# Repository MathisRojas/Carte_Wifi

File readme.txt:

Ce dossier contient l'ensemble des fichiers relatifs à la réalisation au projet :

1. Bilan produit

	Analyse de l'impact environnemental du projet (BBD 2011).

2. Diagrammes

	Inclut les différents schémas et diagrammes nécessaires à la compréhension du projet :

		Diagrammes des cas d'utilisation
		Diagrammes des exigences
		Algorigrammes

3. Documents utiles

	Regroupe les documents de référence et les documents techniques :

		Bibliographie

		Datasheets des composants utilisés :

			SHT21 (capteur d'humidité et de température)
			Relais
			ESP01 (module Wifi)

4. Electronique

	Documents et fichiers de conception électronique :

		Liste des composants électroniques utilisés (prix et référence fournisseur)
		Carte WiFi : fichier KiCad, typons, plan de perçage et d’implémentation, fichiers G-code et FlatCAM pour CNC
		Carte capteurs : fichier KiCad, typons, plan de perçage et d’implémentation

5. Planning

	Inclut le suivi du projet, le planning prévisionnel et l'état d'avancement des différentes étapes.

6. Programmes

	Contient les fichiers et codes liés aux développements logiciels :

		Carte WiFi : Programme C du microcontrôleur (PIC18F26K22)
		Application Node.js : scripts et fichiers de l'application

7.A la racine du dossier :

	Vidéo de présentation
	Manuel d'utilisation
	Rapport technique du projet

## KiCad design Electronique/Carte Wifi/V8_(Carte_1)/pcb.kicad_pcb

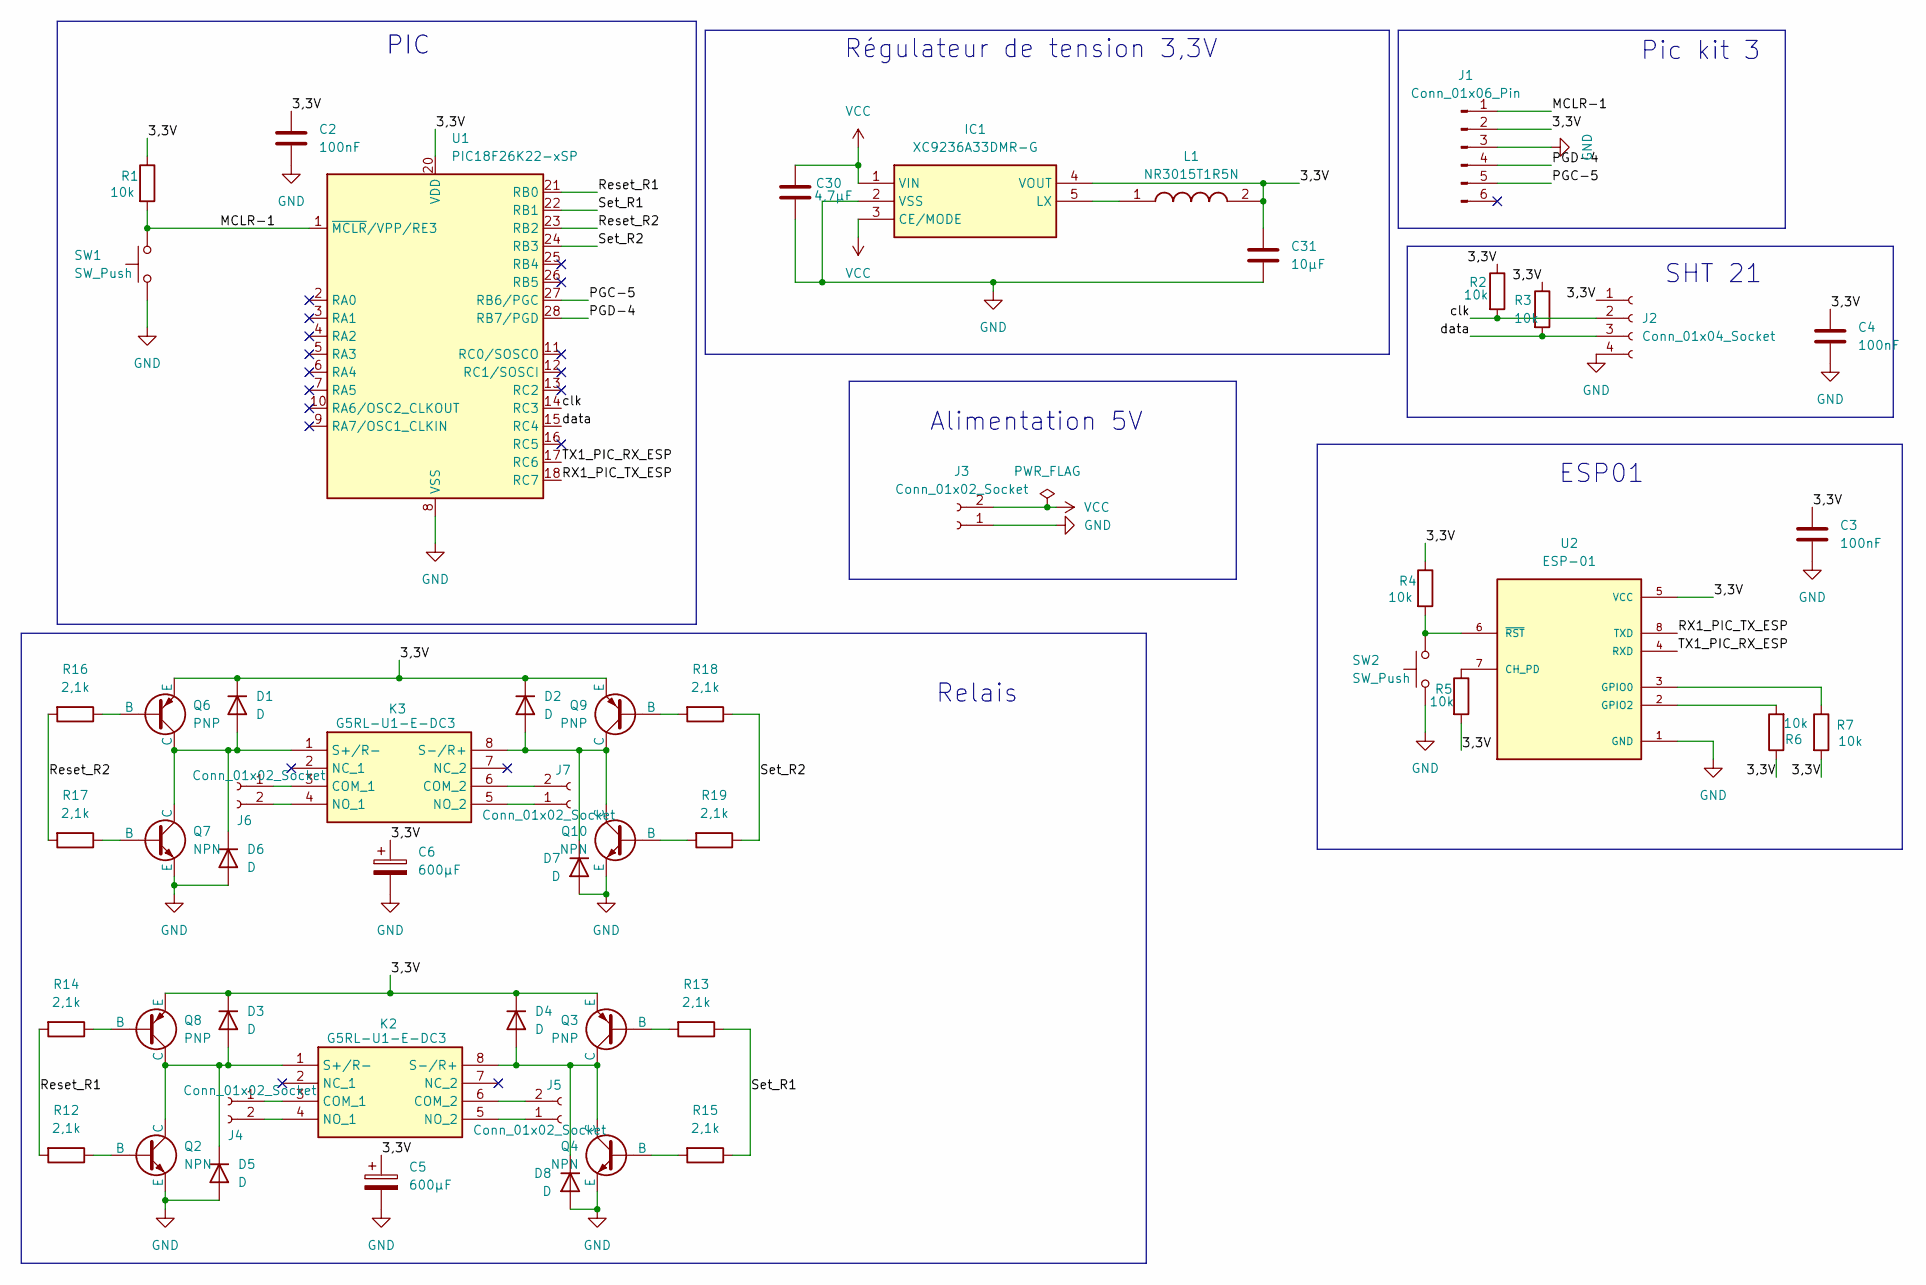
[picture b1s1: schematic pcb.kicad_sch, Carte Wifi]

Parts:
C2, C3, C4: 100nF; IUT_Capa_CMS_1206
C5, C6: 600µF; CP_Radial_D10.0mm_P5.00mm
C30: 4,7µF; IUT_Capa_CMS_1206
C31: 10µF; IUT_Capa_CMS_1206
D1, D2, D3, D4, D5, D6, D7, D8: D; IUT_Diode
IC1: XC9236A33DMR-G; SOT95P280X130-5N; Mouser Part Number 865-XC9236A33DMR-G
J1: Conn_01x06_Pin; IUT_SIL-6
J2: Conn_01x04_Socket; IUT_SIL-4
J3, J4, J5, J6, J7: Conn_01x02_Socket; IUT_bornier2
K2, K3: G5RL-U1-E-DC3; G5RLU1E; Mouser Part Number 653-G5RLU1EDC3
L1: NR3015T1R5N; NR3015; Mouser Part Number 963-NR3015T1R5N
Q2, Q4, Q7, Q10: NPN; 2SCR514RTL
Q3, Q6, Q8, Q9: PNP; SOT95P237X112-3N
R1, R2, R3, R4, R5, R6, R7: 10k; IUT_R4
R12, R13, R14, R15, R16, R17, R18, R19: 2,1k; IUT_R4
SW1, SW2: SW_Push; IUT_BP_petit
U1: PIC18F26K22-xSP; DIP-28_W7.62mm
U2: ESP-01; MODULE_ESP-01; PARTREV 1.0

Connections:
/3,3V: C2.1, C3.1, C4.1, C5.1, C6.1, C31.1, D1.1 (K), D2.1 (K), D3.1 (K), D4.1 (K), IC1.4 (VOUT), J1.2, J2.1, L1.2, Q3.2 (E), Q6.2 (E), Q8.2 (E), Q9.2 (E), R1.1, R2.1, R3.1, R4.1, R5.2, R6.1, R7.2, U1.20 (VDD), U2.5 (VCC)
/MCLR-1: J1.1, R1.2, SW1.2, U1.1 (~MCLR/VPP/RE3)
/PGC-5: J1.5, U1.27 (RB6/PGC)
/PGD-4: J1.4, U1.28 (RB7/PGD)
/RX1_PIC_TX_ESP: U1.18 (RC7), U2.8 (TXD)
/Reset_R1: R12.2, R14.2, U1.21 (RB0)
/Reset_R2: R16.2, R17.2, U1.23 (RB2)
/Set_R1: R13.1, R15.1, U1.22 (RB1)
/Set_R2: R18.1, R19.1, U1.24 (RB3)
/TX1_PIC_RX_ESP: U1.17 (RC6), U2.4 (RXD)
/clk: J2.2, R2.2, U1.14 (RC3)
/data: J2.3, R3.2, U1.15 (RC4)
GND: C2.2, C3.2, C4.2, C5.2, C6.2, C30.2, C31.2, D5.2 (A), D6.2 (A), D7.2 (A), D8.2 (A), IC1.2 (VSS), J1.3, J2.4, J3.1, Q2.2 (E), Q4.2 (E), Q7.2 (E), Q10.2 (E), SW1.1, SW2.1, U1.8 (VSS), U1.19 (VSS), U2.1 (GND)
unnamed: D1.2 (A), D6.1 (K), K3.1 (S+/R-), Q6.3 (C), Q7.3 (C)
unnamed: D2.2 (A), D7.1 (K), K3.8 (S-/R+), Q9.3 (C), Q10.3 (C)
unnamed: D3.2 (A), D5.1 (K), K2.1 (S+/R-), Q2.3 (C), Q8.3 (C)
unnamed: D4.2 (A), D8.1 (K), K2.8 (S-/R+), Q3.3 (C), Q4.3 (C)
unnamed: IC1.5 (LX), L1.1
unnamed: J4.1, K2.3 (COM_1)
unnamed: J4.2, K2.4 (NO_1)
unnamed: J5.1, K2.5 (NO_2)
unnamed: J5.2, K2.6 (COM_2)
unnamed: J6.1, K3.3 (COM_1)
unnamed: J6.2, K3.4 (NO_1)
unnamed: J7.1, K3.5 (NO_2)
unnamed: J7.2, K3.6 (COM_2)
unnamed: Q2.1 (B), R12.1
unnamed: Q3.1 (B), R13.2
unnamed: Q4.1 (B), R15.2
unnamed: Q6.1 (B), R16.1
unnamed: Q7.1 (B), R17.1
unnamed: Q8.1 (B), R14.1
unnamed: Q9.1 (B), R18.2
unnamed: Q10.1 (B), R19.2
unnamed: R5.1, U2.7 (CH_PD)
unnamed: R7.1, U2.3 (GPIO0)
unnamed: R6.2, U2.2 (GPIO2)
unnamed: R4.2, SW2.2, U2.6 (~RST)
VCC: C30.1, IC1.1 (VIN), IC1.3 (CE/MODE), J3.2

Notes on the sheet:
Relais
ESP01
Alimentation 5V
Régulateur de tension 3,3V
Pic kit 3
PIC
SHT 21

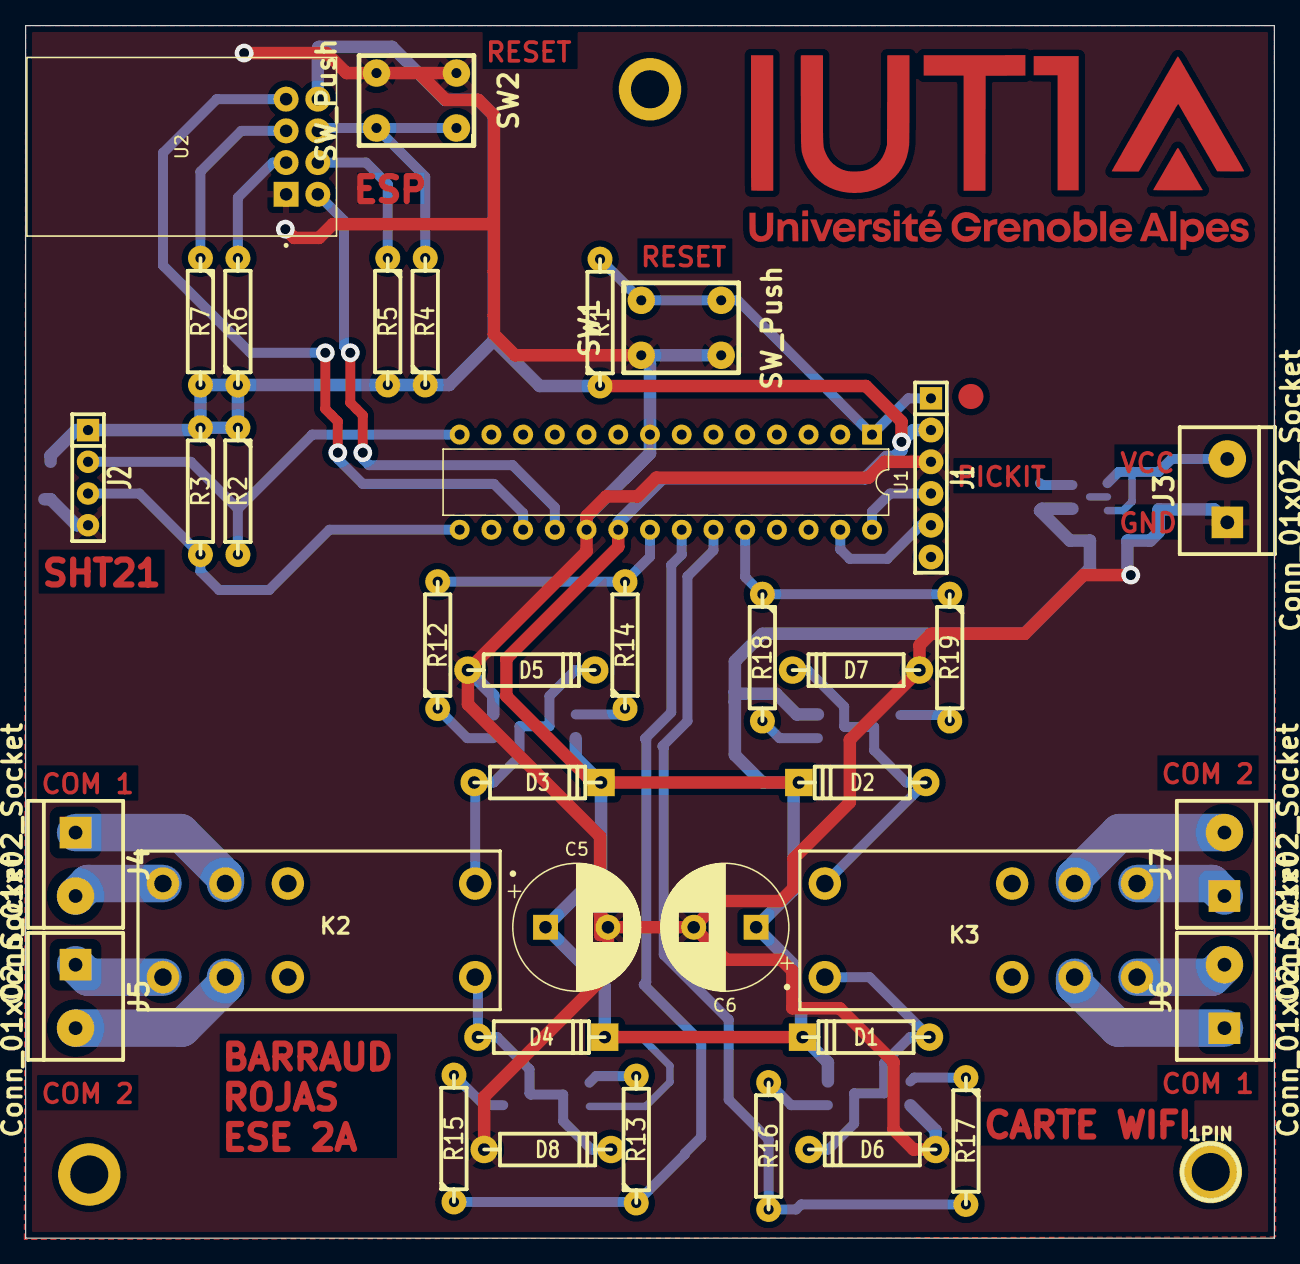
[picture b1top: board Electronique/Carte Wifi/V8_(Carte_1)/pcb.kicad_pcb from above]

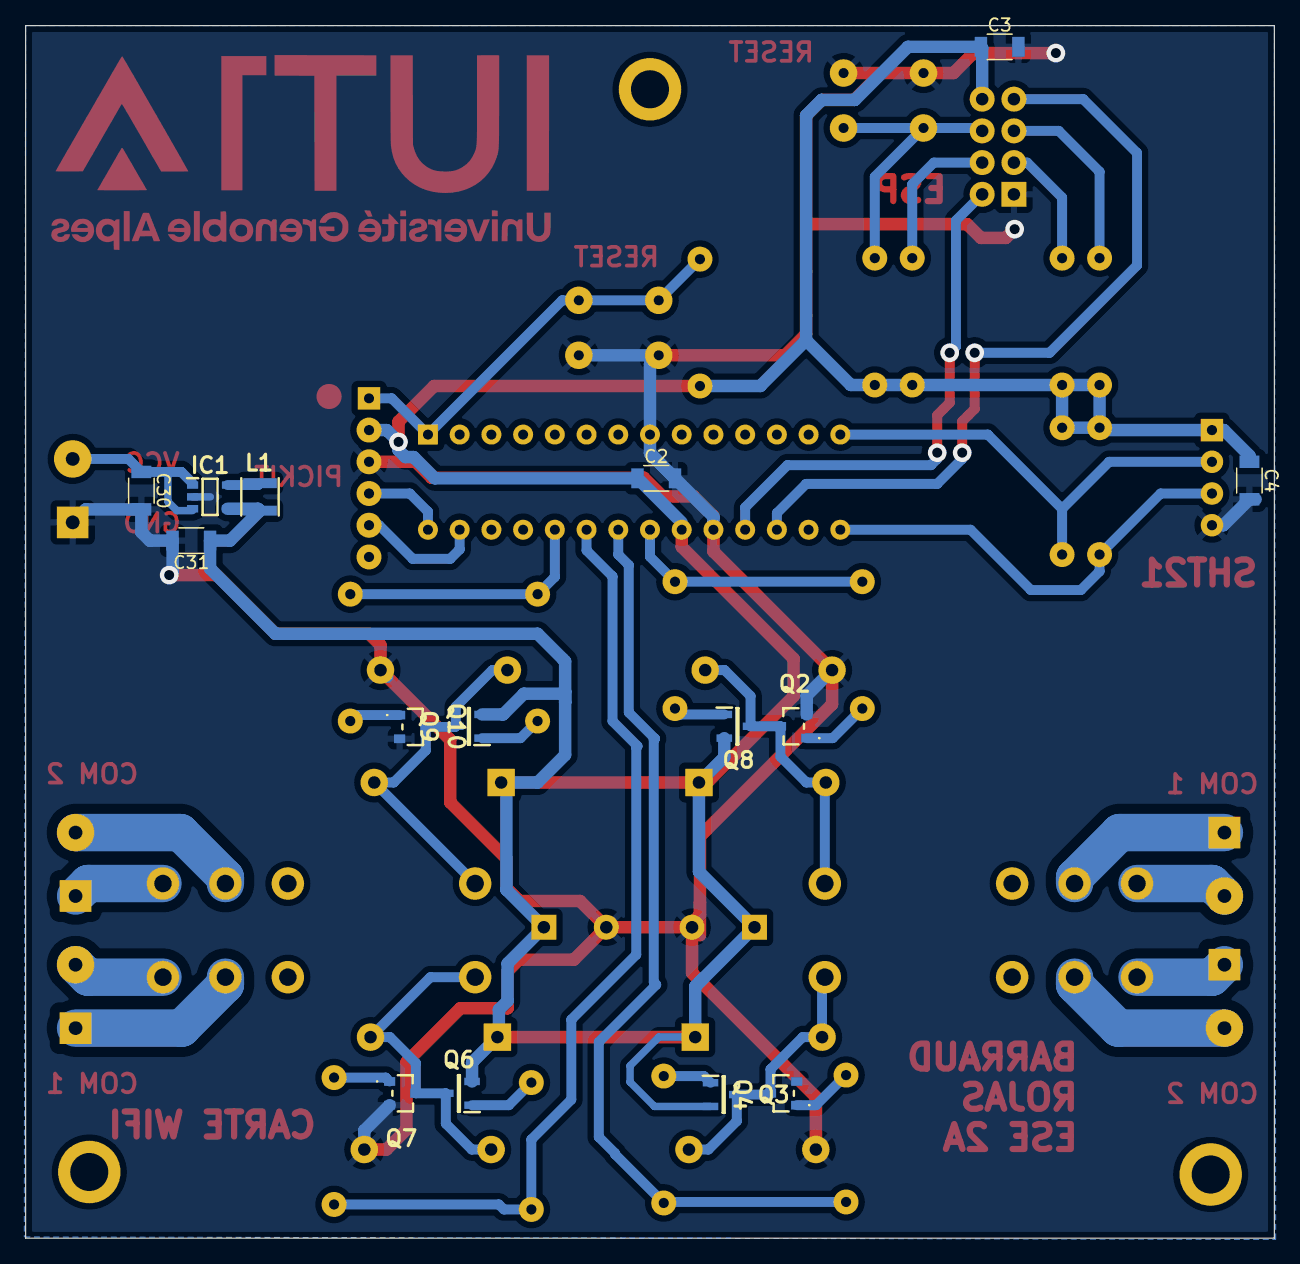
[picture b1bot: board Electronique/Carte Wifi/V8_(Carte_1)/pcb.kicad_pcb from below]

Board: 2 copper layers, 100.0 x 97.1 mm, 54 parts (15 on the bottom side), 39 nets.

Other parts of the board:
1PIN: P***; IUT_TrouFixation

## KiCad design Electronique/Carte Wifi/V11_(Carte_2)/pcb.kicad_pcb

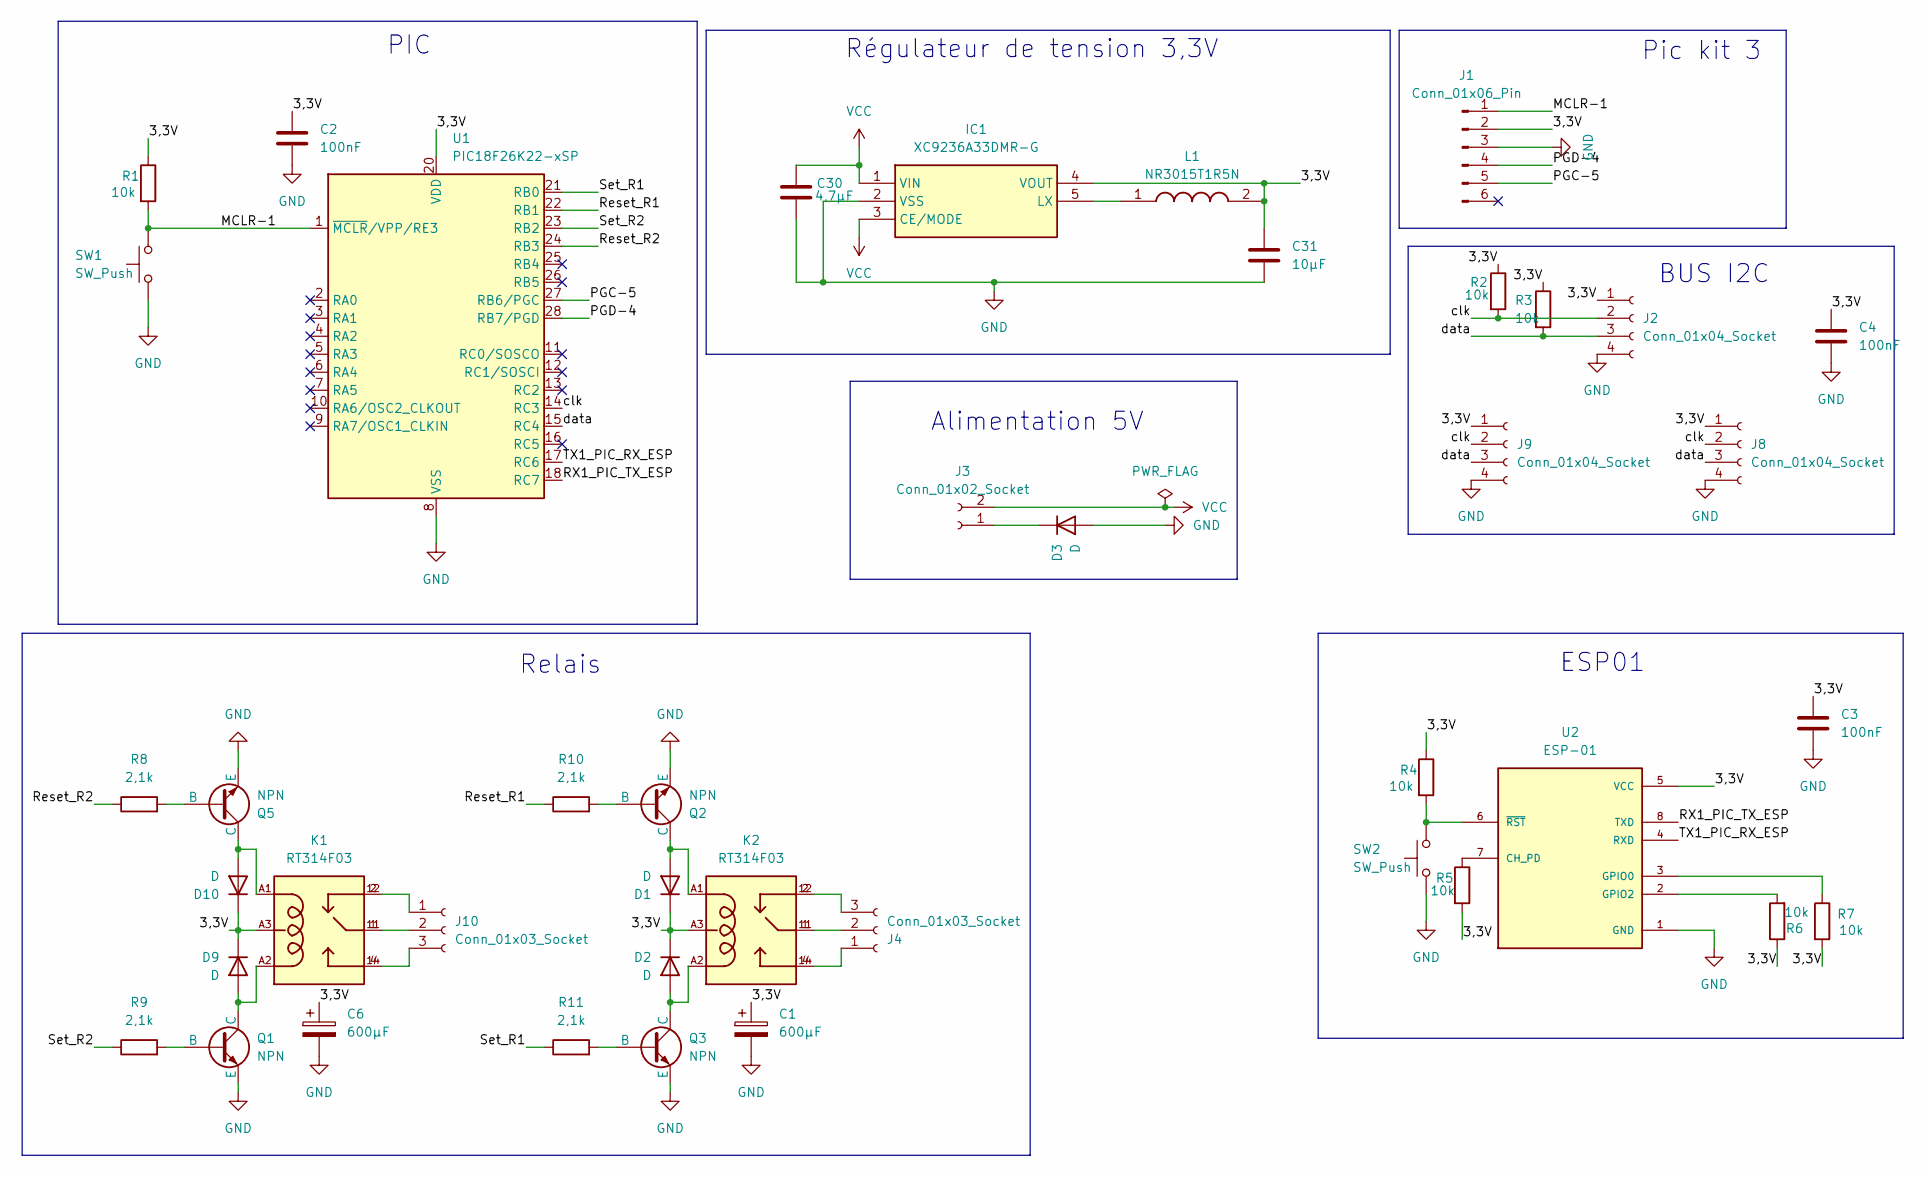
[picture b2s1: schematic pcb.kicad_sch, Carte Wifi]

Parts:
C1, C6: 600µF; CP_Radial_D10.0mm_P5.00mm
C2, C3, C4: 100nF; IUT_Capa_CMS_1206
C30: 4,7µF; IUT_Capa_CMS_1206
C31: 10µF; IUT_Capa_CMS_1206
D1, D2, D3, D9, D10: D; CR_SMA_403AE_OSI-L
IC1: XC9236A33DMR-G; SOT95P280X130-5N; Mouser Part Number 865-XC9236A33DMR-G
J1: Conn_01x06_Pin; IUT_SIL-6
J2, J8, J9: Conn_01x04_Socket; IUT_SIL-4
J3: Conn_01x02_Socket; IUT_bornier2
J4, J10: Conn_01x03_Socket; IUT_bornier3
K1, K2: RT314F03; RELAY_RT314F03; PARTREV 0717
L1: NR3015T1R5N; NR3015; Mouser Part Number 963-NR3015T1R5N
Q1, Q2, Q3, Q5: NPN; 2SCR514RTL
R1, R2, R3, R4, R5, R6, R7: 10k; R_0805_2012Metric
R8, R9, R10, R11: 2,1k; R_0805_2012Metric
SW1, SW2: SW_Push; IUT_BP_petit
U1: PIC18F26K22-xSP; SOP65P780X200-28N
U2: ESP-01; MODULE_ESP-01; PARTREV 1.0

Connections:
/3,3V: C1.1, C2.1, C3.1, C4.1, C6.1, C31.1, D1.1 (K), D2.1 (K), D9.1 (K), D10.1 (K), IC1.4 (VOUT), J1.2, J2.1, J8.1, J9.1, K1.A3, K2.A3, L1.2, R1.1, R2.1, R3.1, R4.1, R5.2, R6.1, R7.2, U1.20 (VDD), U2.5 (VCC)
/MCLR-1: J1.1, R1.2, SW1.2, U1.1 (~MCLR/VPP/RE3)
/PGC-5: J1.5, U1.27 (RB6/PGC)
/PGD-4: J1.4, U1.28 (RB7/PGD)
/RX1_PIC_TX_ESP: U1.18 (RC7), U2.8 (TXD)
/Reset_R1: R10.1, U1.22 (RB1)
/Reset_R2: R8.1, U1.24 (RB3)
/Set_R1: R11.1, U1.21 (RB0)
/Set_R2: R9.1, U1.23 (RB2)
/TX1_PIC_RX_ESP: U1.17 (RC6), U2.4 (RXD)
/clk: J2.2, J8.2, J9.2, R2.2, U1.14 (RC3)
/data: J2.3, J8.3, J9.3, R3.2, U1.15 (RC4)
GND: C1.2, C2.2, C3.2, C4.2, C6.2, C30.2, C31.2, D3.2 (A), IC1.2 (VSS), J1.3, J2.4, J8.4, J9.4, Q1.2 (E), Q2.2 (E), Q3.2 (E), Q5.2 (E), SW1.1, SW2.1, U1.8 (VSS), U1.19 (VSS), U2.1 (GND)
unnamed: D1.2 (A), K2.A1, Q2.3 (C)
unnamed: D2.2 (A), K2.A2, Q3.3 (C)
unnamed: D3.1 (K), J3.1
unnamed: D9.2 (A), K1.A2, Q1.3 (C)
unnamed: D10.2 (A), K1.A1, Q5.3 (C)
unnamed: IC1.5 (LX), L1.1
unnamed: J4.1, K2.4, K2.14
unnamed: J4.2, K2.1, K2.11
unnamed: J4.3, K2.2, K2.12
unnamed: J10.1, K1.2, K1.12
unnamed: J10.2, K1.1, K1.11
unnamed: J10.3, K1.4, K1.14
unnamed: Q1.1 (B), R9.2
unnamed: Q2.1 (B), R10.2
unnamed: Q3.1 (B), R11.2
unnamed: Q5.1 (B), R8.2
unnamed: R5.1, U2.7 (CH_PD)
unnamed: R7.1, U2.3 (GPIO0)
unnamed: R6.2, U2.2 (GPIO2)
unnamed: R4.2, SW2.2, U2.6 (~RST)
VCC: C30.1, IC1.1 (VIN), IC1.3 (CE/MODE), J3.2

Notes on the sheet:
Relais
ESP01
Alimentation 5V
Régulateur de tension 3,3V
Pic kit 3
PIC
BUS I2C

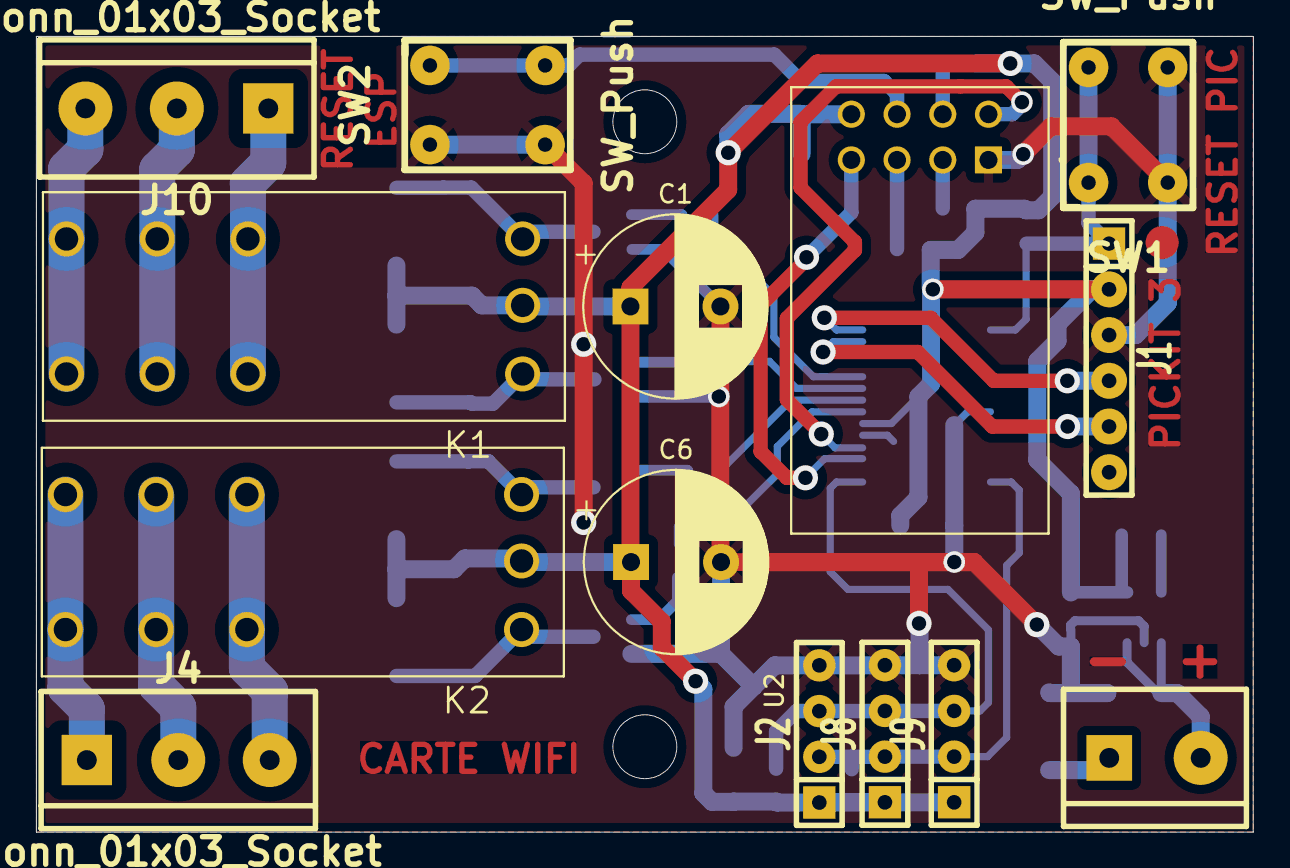
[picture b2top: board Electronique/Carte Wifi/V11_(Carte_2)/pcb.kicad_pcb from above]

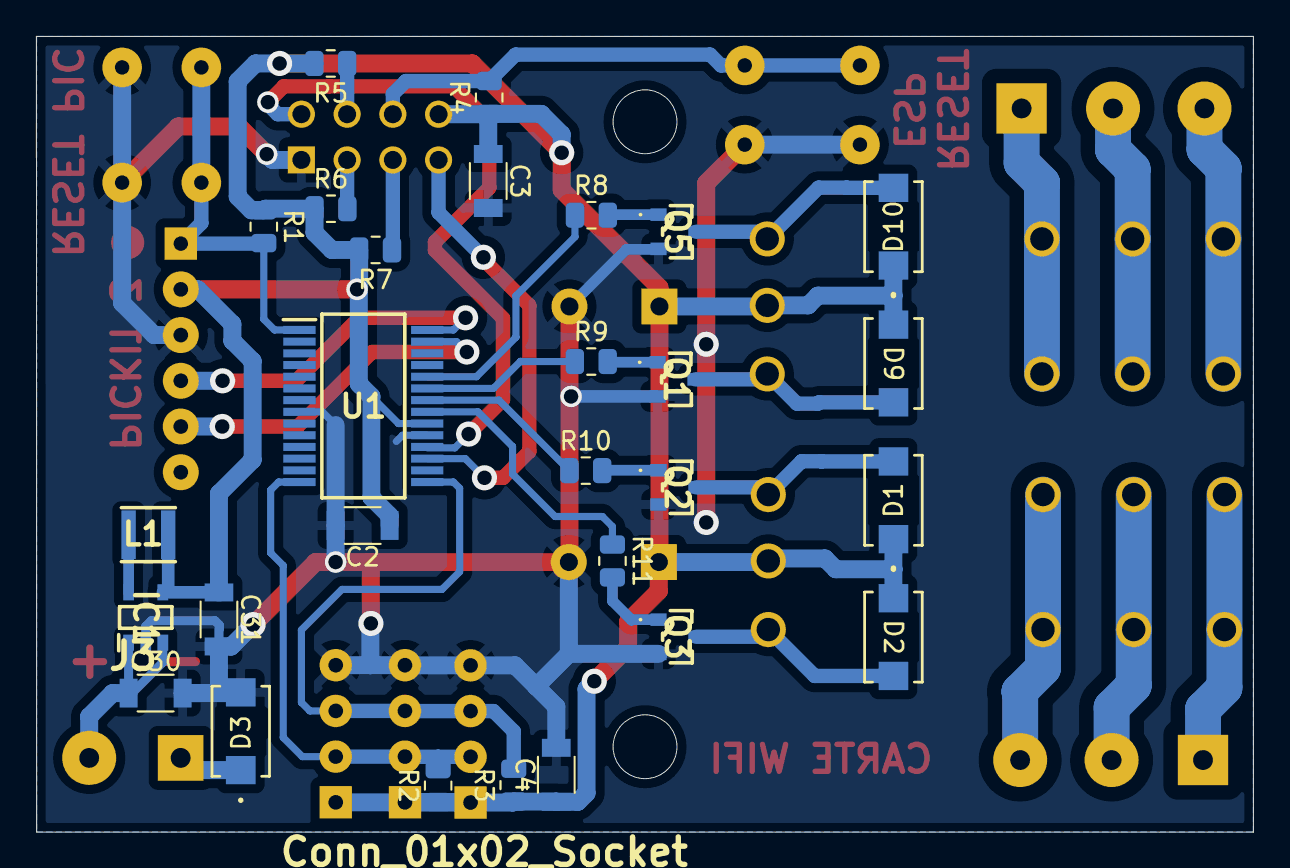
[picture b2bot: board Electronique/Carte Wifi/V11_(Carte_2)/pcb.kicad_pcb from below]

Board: 2 copper layers, 67.6 x 44.2 mm, 42 parts (28 on the bottom side), 34 nets.

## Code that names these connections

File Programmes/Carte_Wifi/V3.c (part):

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

//Définition des entrées/sorties du système
#define Reset_R1  LATBbits.LB0   //commande ouvrir relai 1
#define Set_R1    LATBbits.LB1 //commande fermee relai 1
#define Reset_R2   LATBbits.LB2   //commande ouvrir relai 2
#define Set_R2 LATBbits.LB3   //commande fermee relai 2



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//-----------------------------------------------------------------------------------------------------------------
void R1_ouvert(void)
{
    Set_R1=1;
    __delay_ms(10);
    Set_R1=0; 
}

void R1_fermee(void)
{
    Reset_R1=1;
    __delay_ms(10);
    Reset_R1=0; 
}
void R2_ouvert(void)
{
    Set_R2=1;
    __delay_ms(10);
    Set_R2=0; 
}

void R2_fermee(void)
{
    Reset_R2=1;
    __delay_ms(10);
    Reset_R2=0; 
}

void envoyer_UART(char* buffer)
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//Initialisation des ports d'entrée/sortie

//RB0 (Reset_R1), RB1 (Set_R1), RB2 (Reset_R2), RB3 (Set_R2) en sortie logique numérique
  TRISBbits.RB0=0; //RB0 en sortie
  TRISBbits.RB1=0; //RB1 en sortie
  TRISBbits.RB2=0; //RB2 en sortie 
  TRISBbits.RB3=0; //RB3 en sortie
  ANSELBbits.ANSB0=0;              //désactivation du mode analogique de RB0
  ANSELBbits.ANSB1=0;              //désactivation du mode analogique de RB1
  ANSELBbits.ANSB2=0;              //désactivation du mode analogique de RB2
  ANSELBbits.ANSB3=0;              //désactivation du mode analogique de RB3
  // Configuration des broches I2C
  TRISCbits.RC3 = 1;  // Configurer RC3 (SCL) en entrée
  TRISCbits.RC4 = 1;  // Configurer RC4 (SDA) en entrée
  ANSELCbits.ANSC3=0; //désactivation du mode analogique de RB0
  ANSELCbits.ANSC4=0; //désactivation du mode analogique de RB1

  Reset_R1=0;
  Set_R1=0;
  Reset_R2=0;
  Set_R2=0;

  TEF_bit=0;
  VaON_bit=0;
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
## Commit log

2025-04-15 lien vidéo de présentation
